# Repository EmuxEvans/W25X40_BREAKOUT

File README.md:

# W25X40_BREAKOUT
Breakout board for the W25X40CL Serial flash memory [W25X40CL Serial flash memory](http://www.digikey.com/product-detail/es/winbond-electronics/W25X40CLSNIG/W25X40CLSNIG-ND/3008652)

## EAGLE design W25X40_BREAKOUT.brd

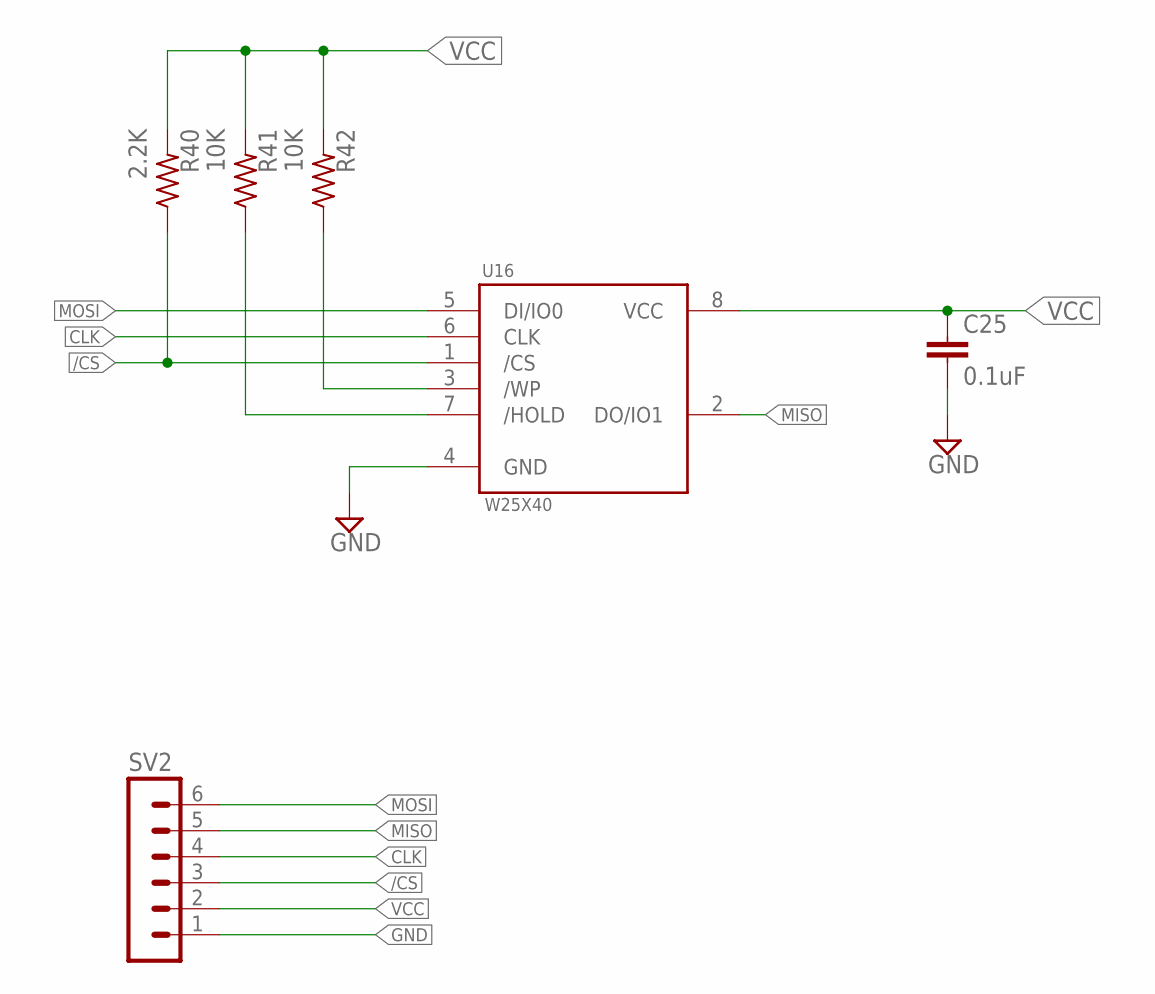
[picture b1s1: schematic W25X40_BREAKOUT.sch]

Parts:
C25: 0.1uF; C025-030X050
R40: 2.2K; 0204/7
R41, R42: 10K; 0204/7
SV2: MA06-1
U16: W25X40CLUXIG; SOIC8

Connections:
/CS: R40.1, SV2.3, U16.1 (/CS)
CLK: SV2.4, U16.6 (CLK)
GND: C25.2, SV2.1, U16.4 (GND)
MISO: SV2.5, U16.2 (DO/IO1)
MOSI: SV2.6, U16.5 (DI/IO0)
unnamed: R41.1, U16.7 (/HOLD)
unnamed: R42.1, U16.3 (/WP)
VCC: C25.1, R40.2, R41.2, R42.2, SV2.2, U16.8 (VCC)

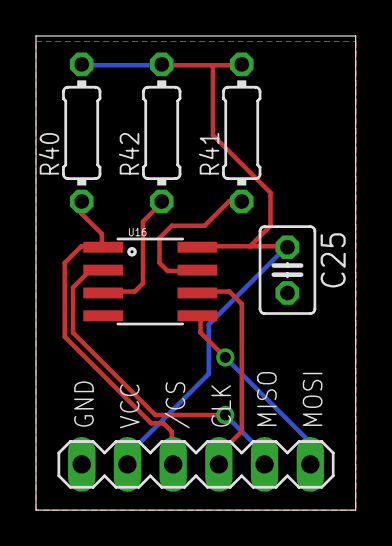
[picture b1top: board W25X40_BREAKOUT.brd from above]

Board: 2 copper layers, 17.8 x 26.3 mm, 6 parts (0 on the bottom side), 8 nets.

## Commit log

2016-06-08 .sch and .brd files added
2016-06-08 Image of the schematic added
2016-06-08 Link of the component and image added to readme
